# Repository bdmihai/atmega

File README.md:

# atmega
atmega repository for the DCF77 Clock

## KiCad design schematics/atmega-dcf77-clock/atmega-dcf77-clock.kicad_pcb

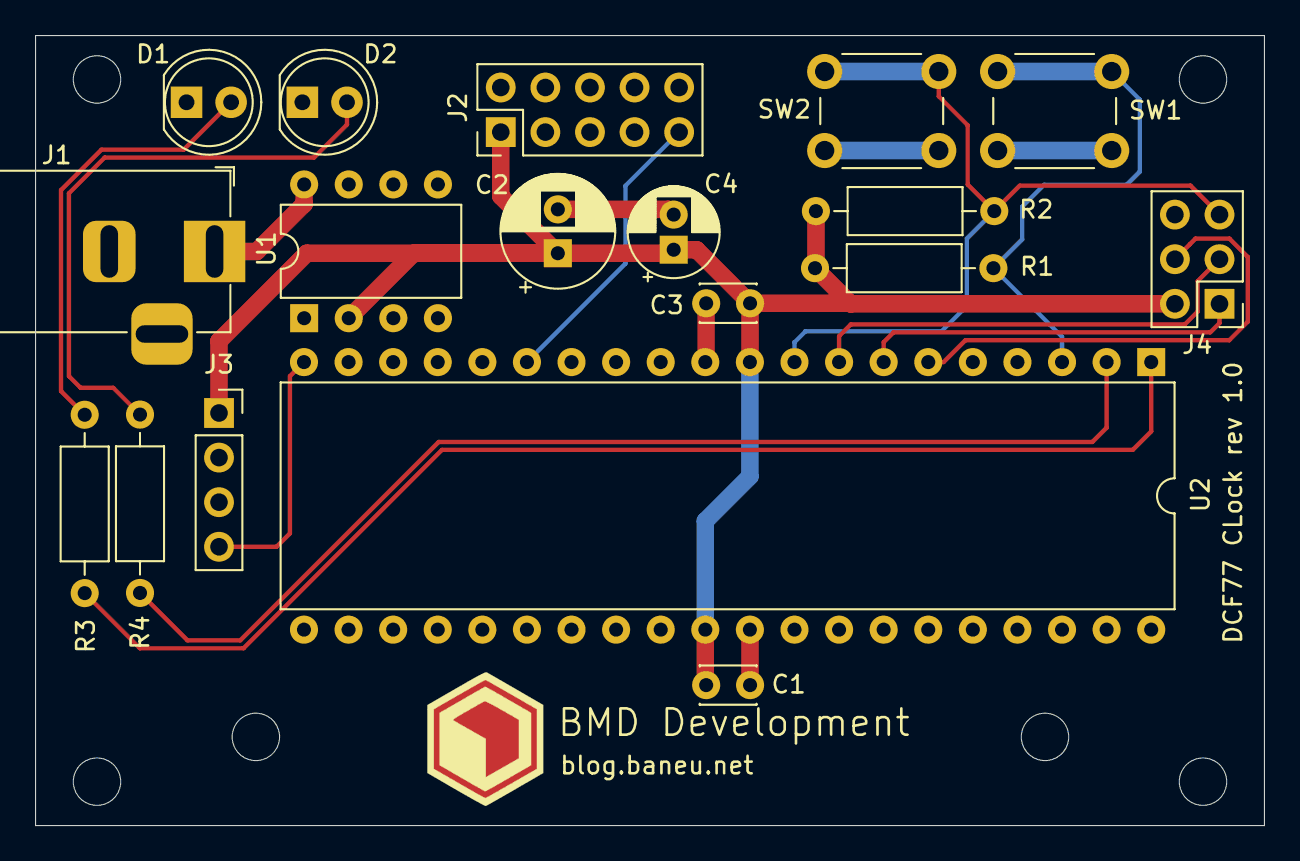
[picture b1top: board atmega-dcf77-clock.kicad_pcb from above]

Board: 2 copper layers, 70.0 x 45.0 mm, 19 parts (1 on the bottom side), 14 nets.

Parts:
C1, C3: 100n; C_Disc_D3.0mm_W2.0mm_P2.50mm
C2: 100u; CP_Radial_D6.3mm_P2.50mm
C4: 10u; CP_Radial_D5.0mm_P2.00mm
D1: LED G; LED_D5.0mm
D2: LED R; LED_D5.0mm
J1: Barrel_Jack; BarrelJack_Horizontal
J2: LCD Module; PinSocket_2x05_P2.54mm_Vertical
J3: DCF77 Receiver Module; PinSocket_1x04_P2.54mm_Vertical
J4: Conn_02x03_Odd_Even; PinHeader_2x03_P2.54mm_Vertical
R1, R2: 10k; R_Axial_DIN0207_L6.3mm_D2.5mm_P10.16mm_Horizontal
R3, R4: 330; R_Axial_DIN0207_L6.3mm_D2.5mm_P10.16mm_Horizontal
Ref**: Val**; kicad_icon
SW1: SW_LIGHT; SW_PUSH_6mm
SW2: SW_RESET; SW_PUSH_6mm
U1: MAX667; DIP-8_W7.62mm
U2: ATmega324PA-PU; DIP-40_W15.24mm

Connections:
+5V: C1.1, C2.1, C3.1, C4.1, J2.1, J3.1, J4.2, R1.1, R2.1, U1.2, U2.10, U2.30
GND: C1.2, C2.2, C3.2, C4.2, D1.1, D2.1, J1.2, J2.10, J3.2, J3.3, J4.6, SW1.2, SW2.1, U1.4, U1.5, U1.6, U2.11, U2.31
MISO: J4.1, U2.7
MOSI: J4.4, U2.6
unnamed: D1.2, R3.1
unnamed: D2.2, R4.2
unnamed: J1.1, U1.8
unnamed: J2.9, U2.15
unnamed: J3.4, U2.20
unnamed: R3.2, U2.1
unnamed: R4.1, U2.2
RST: J4.5, R2.2, SW2.2, U2.9
SCK: J4.3, U2.8
SW_Light: R1.2, SW1.1, U2.3

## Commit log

2020-05-04 initial revision
2020-05-13 Fixed PCB/small fixes
2020-05-30 Added case
